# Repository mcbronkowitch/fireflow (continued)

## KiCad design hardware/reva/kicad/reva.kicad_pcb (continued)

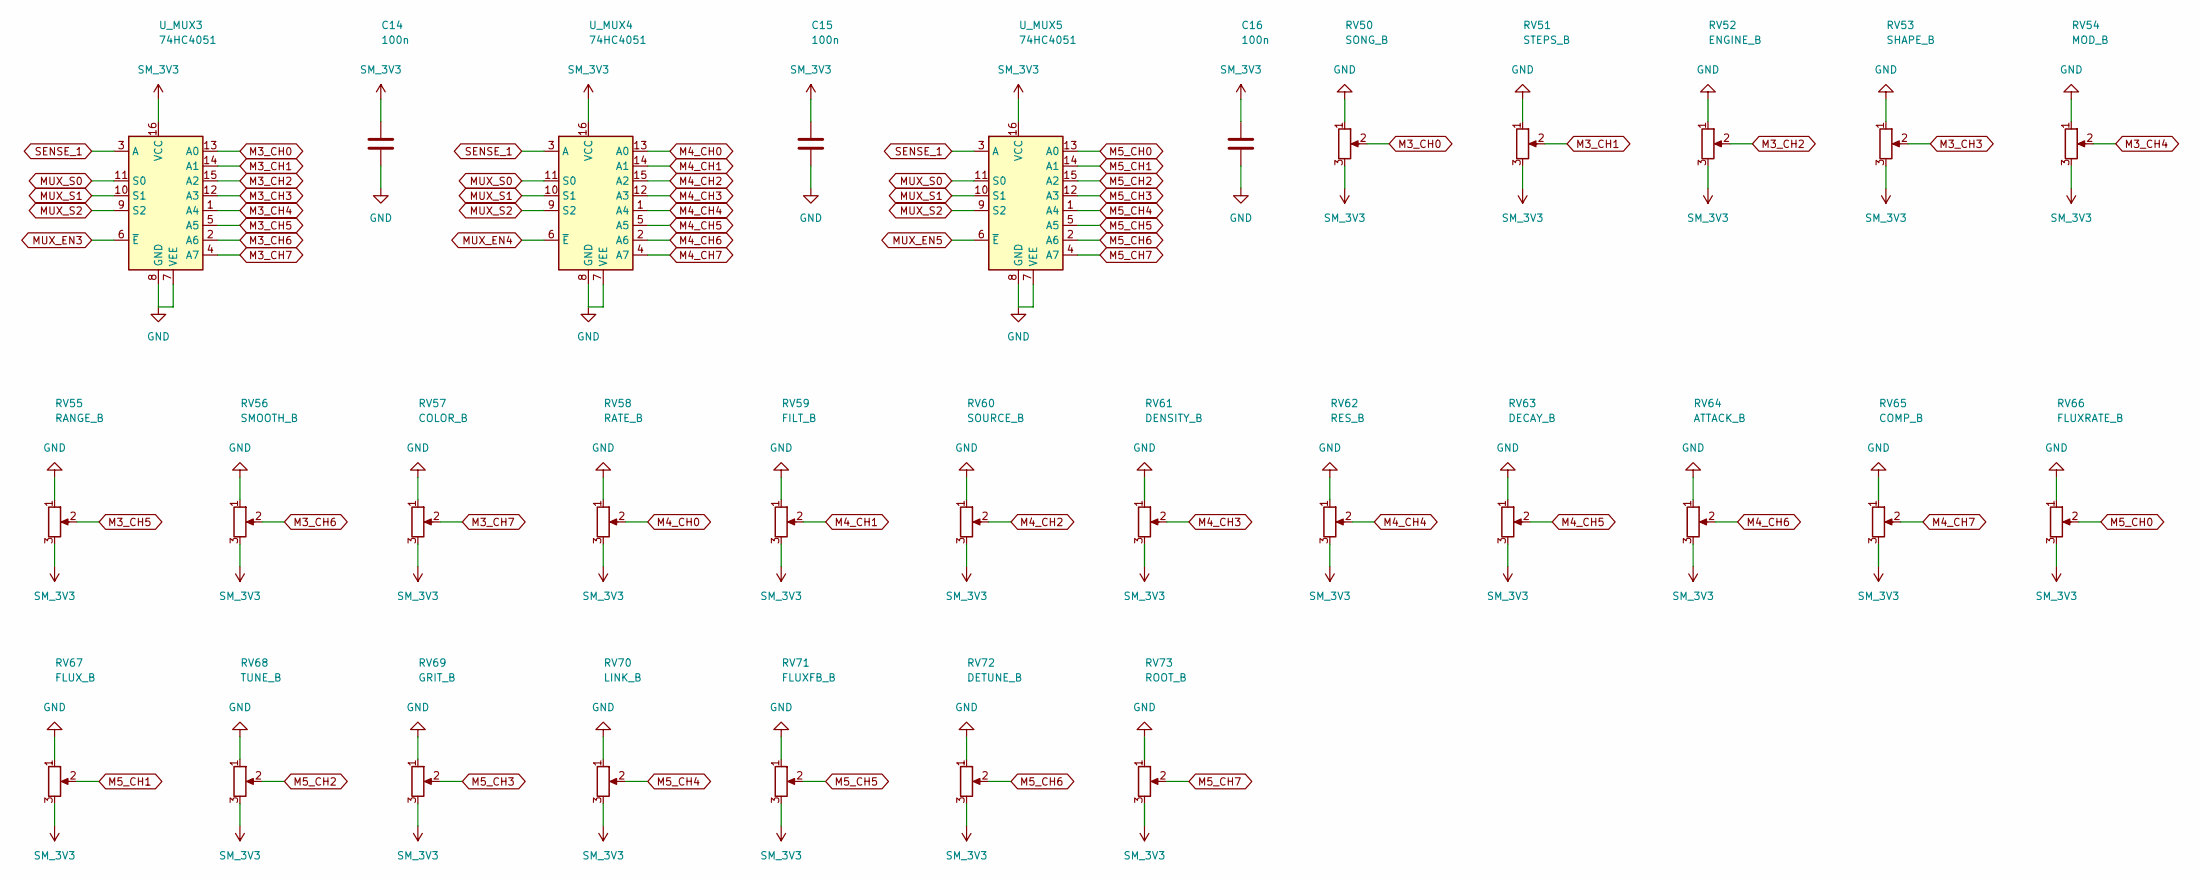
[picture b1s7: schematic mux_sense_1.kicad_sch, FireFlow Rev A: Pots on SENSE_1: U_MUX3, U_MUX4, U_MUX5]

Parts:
C14, C15, C16: 100n; C_0603_1608Metric; LCSC C14663
RV50: SONG_B; Potentiometer_Alpha_RD901F-40-00D_Single_Vertical
RV51: STEPS_B; Potentiometer_Alpha_RD901F-40-00D_Single_Vertical
RV52: ENGINE_B; Potentiometer_Alpha_RD901F-40-00D_Single_Vertical
RV53: SHAPE_B; Potentiometer_Alpha_RD901F-40-00D_Single_Vertical
RV54: MOD_B; Potentiometer_Alpha_RD901F-40-00D_Single_Vertical
RV55: RANGE_B; Potentiometer_Alpha_RD901F-40-00D_Single_Vertical
RV56: SMOOTH_B; Potentiometer_Alpha_RD901F-40-00D_Single_Vertical
RV57: COLOR_B; Potentiometer_Alpha_RD901F-40-00D_Single_Vertical
RV58: RATE_B; Potentiometer_Alpha_RD901F-40-00D_Single_Vertical
RV59: FILT_B; Potentiometer_Alpha_RD901F-40-00D_Single_Vertical
RV60: SOURCE_B; Potentiometer_Alpha_RD901F-40-00D_Single_Vertical
RV61: DENSITY_B; Potentiometer_Alpha_RD901F-40-00D_Single_Vertical
RV62: RES_B; Potentiometer_Alpha_RD901F-40-00D_Single_Vertical
RV63: DECAY_B; Potentiometer_Alpha_RD901F-40-00D_Single_Vertical
RV64: ATTACK_B; Potentiometer_Alpha_RD901F-40-00D_Single_Vertical
RV65: COMP_B; Potentiometer_Alpha_RD901F-40-00D_Single_Vertical
RV66: FLUXRATE_B; Potentiometer_Alpha_RD901F-40-00D_Single_Vertical
RV67: FLUX_B; Potentiometer_Alpha_RD901F-40-00D_Single_Vertical
RV68: TUNE_B; Potentiometer_Alpha_RD901F-40-00D_Single_Vertical
RV69: GRIT_B; Potentiometer_Alpha_RD901F-40-00D_Single_Vertical
RV70: LINK_B; Potentiometer_Alpha_RD901F-40-00D_Single_Vertical
RV71: FLUXFB_B; Potentiometer_Alpha_RD901F-40-00D_Single_Vertical
RV72: DETUNE_B; Potentiometer_Alpha_RD901F-40-00D_Single_Vertical
RV73: ROOT_B; Potentiometer_Alpha_RD901F-40-00D_Single_Vertical
U_MUX3, U_MUX4, U_MUX5: 74HC4051; SOIC-16_3.9x9.9mm_P1.27mm; LCSC C9386

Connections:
GND: C14.2, C15.2, C16.2, RV50.1, RV51.1, RV52.1, RV53.1, RV54.1, RV55.1, RV56.1, RV57.1, RV58.1, RV59.1, RV60.1, RV61.1, RV62.1, RV63.1, RV64.1, RV65.1, RV66.1, RV67.1, RV68.1, RV69.1, RV70.1, RV71.1, RV72.1, RV73.1, U_MUX3.7 (VEE), U_MUX3.8 (GND), U_MUX4.7 (VEE), U_MUX4.8 (GND), U_MUX5.7 (VEE), U_MUX5.8 (GND); also elsewhere on the board
M3_CH0: RV50.2, U_MUX3.13 (A0)
M3_CH1: RV51.2, U_MUX3.14 (A1)
M3_CH2: RV52.2, U_MUX3.15 (A2)
M3_CH3: RV53.2, U_MUX3.12 (A3)
M3_CH4: RV54.2, U_MUX3.1 (A4)
M3_CH5: RV55.2, U_MUX3.5 (A5)
M3_CH6: RV56.2, U_MUX3.2 (A6)
M3_CH7: RV57.2, U_MUX3.4 (A7)
M4_CH0: RV58.2, U_MUX4.13 (A0)
M4_CH1: RV59.2, U_MUX4.14 (A1)
M4_CH2: RV60.2, U_MUX4.15 (A2)
M4_CH3: RV61.2, U_MUX4.12 (A3)
M4_CH4: RV62.2, U_MUX4.1 (A4)
M4_CH5: RV63.2, U_MUX4.5 (A5)
M4_CH6: RV64.2, U_MUX4.2 (A6)
M4_CH7: RV65.2, U_MUX4.4 (A7)
M5_CH0: RV66.2, U_MUX5.13 (A0)
M5_CH1: RV67.2, U_MUX5.14 (A1)
M5_CH2: RV68.2, U_MUX5.15 (A2)
M5_CH3: RV69.2, U_MUX5.12 (A3)
M5_CH4: RV70.2, U_MUX5.1 (A4)
M5_CH5: RV71.2, U_MUX5.5 (A5)
M5_CH6: RV72.2, U_MUX5.2 (A6)
M5_CH7: RV73.2, U_MUX5.4 (A7)
MUX_EN3: U_MUX3.6 (~E); also elsewhere on the board
MUX_EN4: U_MUX4.6 (~E); also elsewhere on the board
MUX_EN5: U_MUX5.6 (~E); also elsewhere on the board
MUX_S0: U_MUX3.11 (S0), U_MUX4.11 (S0), U_MUX5.11 (S0); also elsewhere on the board
MUX_S1: U_MUX3.10 (S1), U_MUX4.10 (S1), U_MUX5.10 (S1); also elsewhere on the board
MUX_S2: U_MUX3.9 (S2), U_MUX4.9 (S2), U_MUX5.9 (S2); also elsewhere on the board
SENSE_1: U_MUX3.3 (A), U_MUX4.3 (A), U_MUX5.3 (A); also elsewhere on the board
SM_3V3: C14.1, C15.1, C16.1, RV50.3, RV51.3, RV52.3, RV53.3, RV54.3, RV55.3, RV56.3, RV57.3, RV58.3, RV59.3, RV60.3, RV61.3, RV62.3, RV63.3, RV64.3, RV65.3, RV66.3, RV67.3, RV68.3, RV69.3, RV70.3, RV71.3, RV72.3, RV73.3, U_MUX3.16 (VCC), U_MUX4.16 (VCC), U_MUX5.16 (VCC); also elsewhere on the board

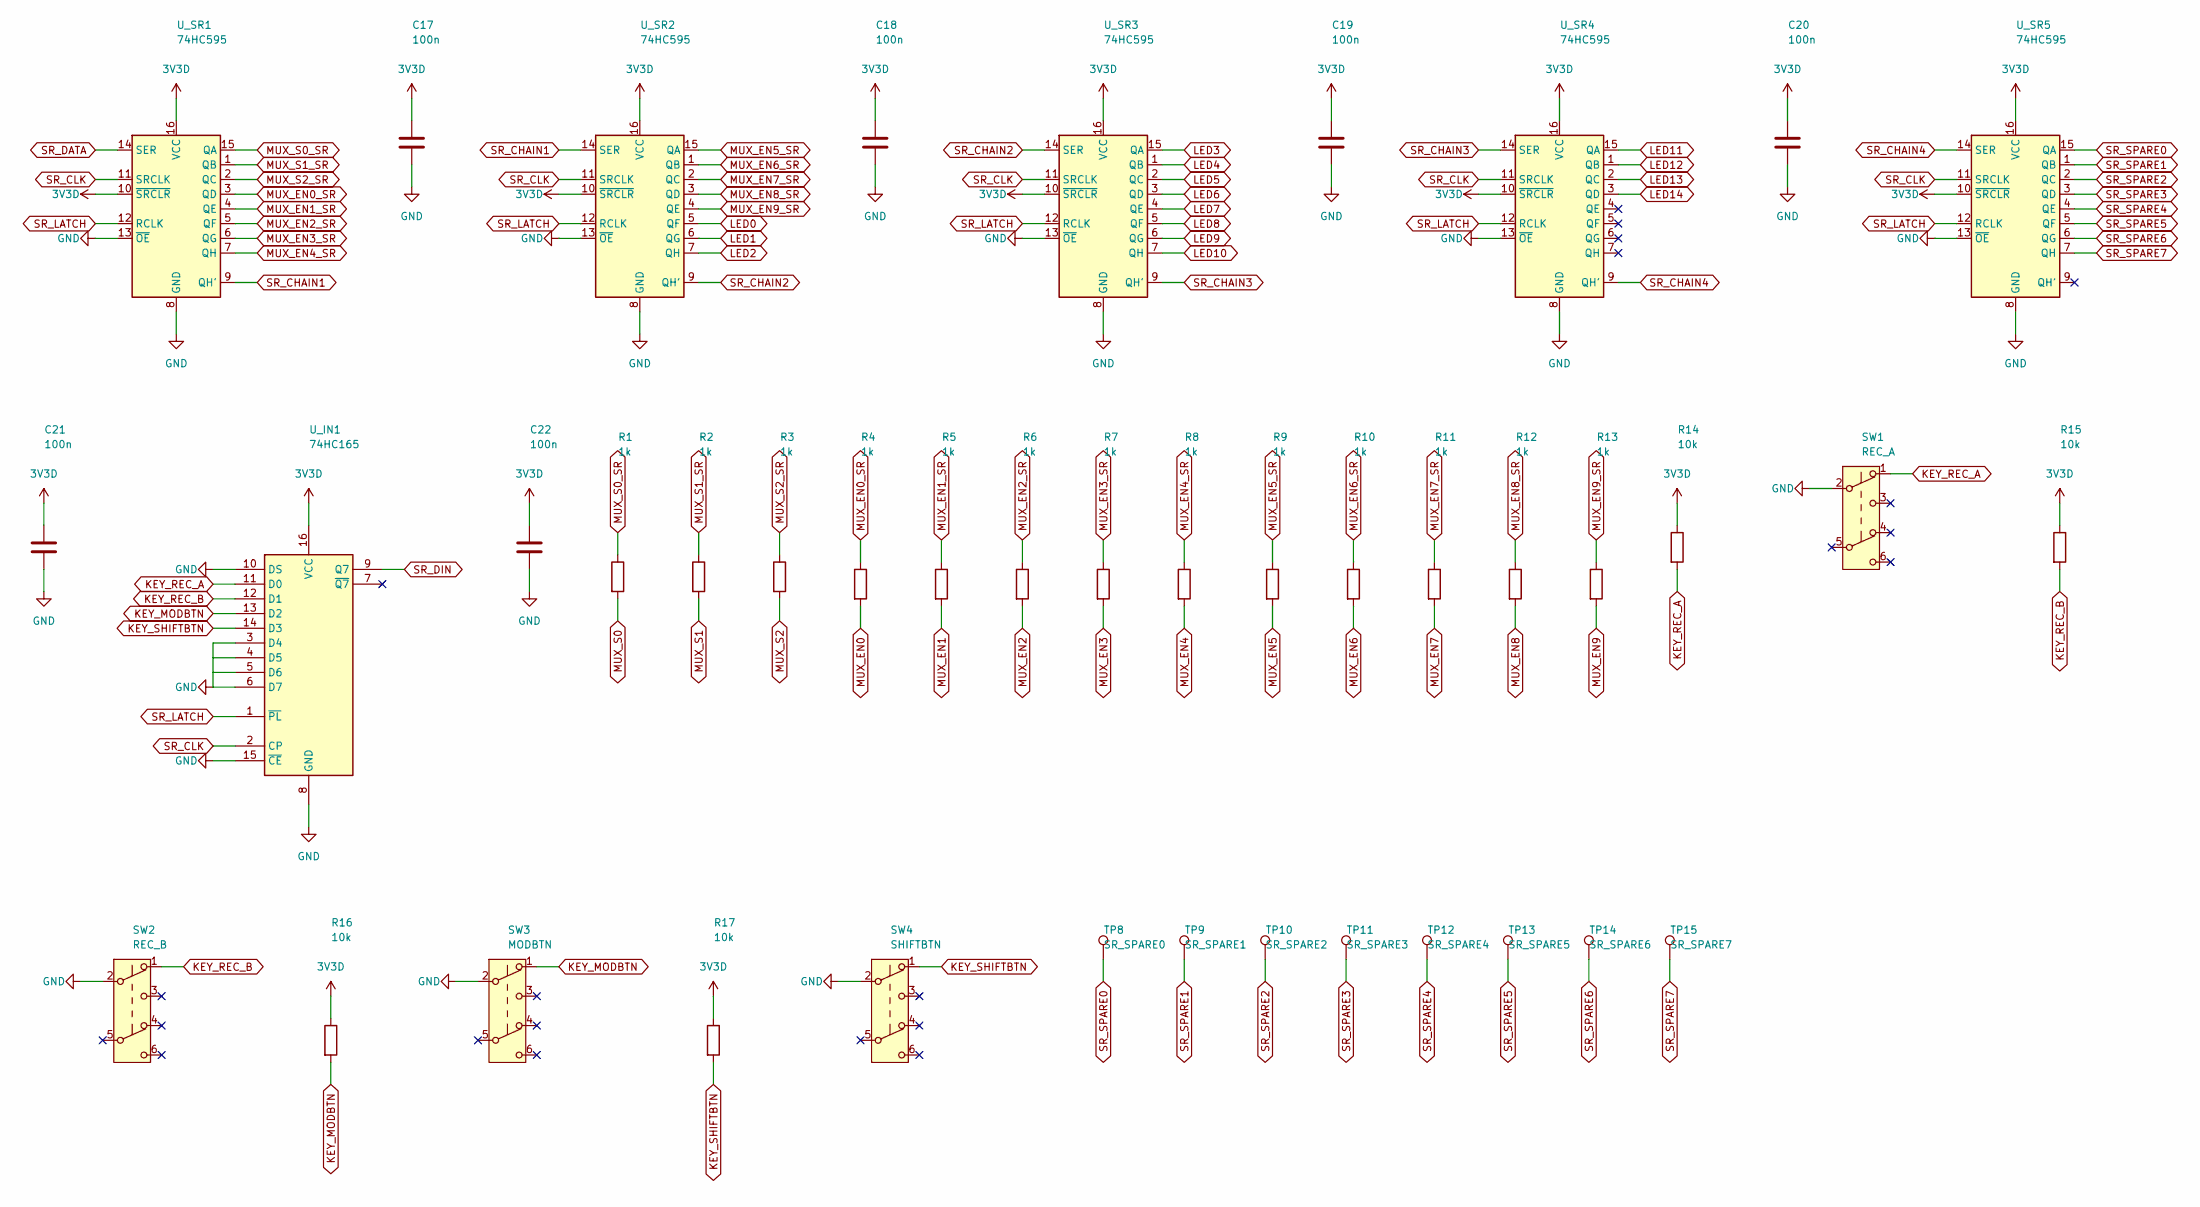
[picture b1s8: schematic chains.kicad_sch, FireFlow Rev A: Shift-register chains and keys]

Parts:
C17, C18, C19, C20, C21, C22: 100n; C_0603_1608Metric; LCSC C14663
R1, R2, R3, R4, R5, R6, R7, R8, R9, R10, R11, R12, R13: 1k; R_0603_1608Metric; LCSC C21190
R14, R15, R16, R17: 10k; R_0603_1608Metric; LCSC C25804
SW1: REC_A; SW_Push_LP_Button
SW2: REC_B; SW_Push_LP_Button
SW3: MODBTN; SW_Push_LP_Button
SW4: SHIFTBTN; SW_Push_LP_Button
TP8: SR_SPARE0; TestPoint_Pad_D1.5mm
TP9: SR_SPARE1; TestPoint_Pad_D1.5mm
TP10: SR_SPARE2; TestPoint_Pad_D1.5mm
TP11: SR_SPARE3; TestPoint_Pad_D1.5mm
TP12: SR_SPARE4; TestPoint_Pad_D1.5mm
TP13: SR_SPARE5; TestPoint_Pad_D1.5mm
TP14: SR_SPARE6; TestPoint_Pad_D1.5mm
TP15: SR_SPARE7; TestPoint_Pad_D1.5mm
U_IN1: 74HC165; SOIC-16_3.9x9.9mm_P1.27mm; LCSC C5613
U_SR1, U_SR2, U_SR3, U_SR4, U_SR5: 74HC595; SOIC-16_3.9x9.9mm_P1.27mm; LCSC C5947

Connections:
3V3D: C17.1, C18.1, C19.1, C20.1, C21.1, C22.1, R14.1, R15.1, R16.1, R17.1, U_IN1.16 (VCC), U_SR1.10 (~SRCLR), U_SR1.16 (VCC), U_SR2.10 (~SRCLR), U_SR2.16 (VCC), U_SR3.10 (~SRCLR), U_SR3.16 (VCC), U_SR4.10 (~SRCLR), U_SR4.16 (VCC), U_SR5.10 (~SRCLR), U_SR5.16 (VCC); also elsewhere on the board
GND: C17.2, C18.2, C19.2, C20.2, C21.2, C22.2, SW1.2 (B), SW2.2 (B), SW3.2 (B), SW4.2 (B), U_IN1.3 (D4), U_IN1.4 (D5), U_IN1.5 (D6), U_IN1.6 (D7), U_IN1.8 (GND), U_IN1.10 (DS), U_IN1.15 (~CE), U_SR1.8 (GND), U_SR1.13 (~OE), U_SR2.8 (GND), U_SR2.13 (~OE), U_SR3.8 (GND), U_SR3.13 (~OE), U_SR4.8 (GND), U_SR4.13 (~OE), U_SR5.8 (GND), U_SR5.13 (~OE); also elsewhere on the board
KEY_MODBTN: R16.2, SW3.1 (A), U_IN1.13 (D2)
KEY_REC_A: R14.2, SW1.1 (A), U_IN1.11 (D0)
KEY_REC_B: R15.2, SW2.1 (A), U_IN1.12 (D1)
KEY_SHIFTBTN: R17.2, SW4.1 (A), U_IN1.14 (D3)
LED0: U_SR2.5 (QF); also elsewhere on the board
LED1: U_SR2.6 (QG); also elsewhere on the board
LED2: U_SR2.7 (QH); also elsewhere on the board
LED3: U_SR3.15 (QA); also elsewhere on the board
LED4: U_SR3.1 (QB); also elsewhere on the board
LED5: U_SR3.2 (QC); also elsewhere on the board
LED6: U_SR3.3 (QD); also elsewhere on the board
LED7: U_SR3.4 (QE); also elsewhere on the board
LED8: U_SR3.5 (QF); also elsewhere on the board
LED9: U_SR3.6 (QG); also elsewhere on the board
LED10: U_SR3.7 (QH); also elsewhere on the board
LED11: U_SR4.15 (QA); also elsewhere on the board
LED12: U_SR4.1 (QB); also elsewhere on the board
LED13: U_SR4.2 (QC); also elsewhere on the board
LED14: U_SR4.3 (QD); also elsewhere on the board
MUX_EN0: R4.2; also elsewhere on the board
MUX_EN0_SR: R4.1, U_SR1.3 (QD)
MUX_EN1: R5.2; also elsewhere on the board
MUX_EN1_SR: R5.1, U_SR1.4 (QE)
MUX_EN2: R6.2; also elsewhere on the board
MUX_EN2_SR: R6.1, U_SR1.5 (QF)
MUX_EN3: R7.2; also elsewhere on the board
MUX_EN3_SR: R7.1, U_SR1.6 (QG)
MUX_EN4: R8.2; also elsewhere on the board
MUX_EN4_SR: R8.1, U_SR1.7 (QH)
MUX_EN5: R9.2; also elsewhere on the board
MUX_EN5_SR: R9.1, U_SR2.15 (QA)
MUX_EN6: R10.2; also elsewhere on the board
MUX_EN6_SR: R10.1, U_SR2.1 (QB)
MUX_EN7: R11.2; also elsewhere on the board
MUX_EN7_SR: R11.1, U_SR2.2 (QC)
MUX_EN8: R12.2; also elsewhere on the board
MUX_EN8_SR: R12.1, U_SR2.3 (QD)
MUX_EN9: R13.2; also elsewhere on the board
MUX_EN9_SR: R13.1, U_SR2.4 (QE)
MUX_S0: R1.2; also elsewhere on the board
MUX_S0_SR: R1.1, U_SR1.15 (QA)
MUX_S1: R2.2; also elsewhere on the board
MUX_S1_SR: R2.1, U_SR1.1 (QB)
MUX_S2: R3.2; also elsewhere on the board
MUX_S2_SR: R3.1, U_SR1.2 (QC)
SR_CHAIN1: U_SR1.9 (QH'), U_SR2.14 (SER)
SR_CHAIN2: U_SR2.9 (QH'), U_SR3.14 (SER)
SR_CHAIN3: U_SR3.9 (QH'), U_SR4.14 (SER)
SR_CHAIN4: U_SR4.9 (QH'), U_SR5.14 (SER)
SR_CLK: U_IN1.2 (CP), U_SR1.11 (SRCLK), U_SR2.11 (SRCLK), U_SR3.11 (SRCLK), U_SR4.11 (SRCLK), U_SR5.11 (SRCLK); also elsewhere on the board
SR_DATA: U_SR1.14 (SER); also elsewhere on the board
SR_DIN: U_IN1.9 (Q7); also elsewhere on the board
SR_LATCH: U_IN1.1 (~PL), U_SR1.12 (RCLK), U_SR2.12 (RCLK), U_SR3.12 (RCLK), U_SR4.12 (RCLK), U_SR5.12 (RCLK); also elsewhere on the board
SR_SPARE0: TP8.1, U_SR5.15 (QA)
SR_SPARE1: TP9.1, U_SR5.1 (QB)
SR_SPARE2: TP10.1, U_SR5.2 (QC)
SR_SPARE3: TP11.1, U_SR5.3 (QD)
SR_SPARE4: TP12.1, U_SR5.4 (QE)
SR_SPARE5: TP13.1, U_SR5.5 (QF)
SR_SPARE6: TP14.1, U_SR5.6 (QG)
SR_SPARE7: TP15.1, U_SR5.7 (QH)

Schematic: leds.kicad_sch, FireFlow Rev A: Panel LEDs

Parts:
D1: SHIFTBTN_L; LED_D3.0mm
D2: SONG_A_L; LED_D3.0mm
D3: GATE_A_L; LED_D3.0mm
D4: FTIME_A_L; LED_D3.0mm
D5: LVL_A_L; LED_D3.0mm
D6: REC_A_L; LED_D3.0mm
D7: CLK_L; LED_D3.0mm
D8: TEMPO_L; LED_D3.0mm
D9: RST_L; LED_D3.0mm
D10: REC_B_L; LED_D3.0mm
D11: LVL_B_L; LED_D3.0mm
D12: FTIME_B_L; LED_D3.0mm
D13: SONG_B_L; LED_D3.0mm
D14: GATE_B_L; LED_D3.0mm
D15: MODBTN_L; LED_D3.0mm
R18, R19, R20, R21, R22, R23, R24, R25, R26, R27, R28, R29, R30, R31, R32: 1k; R_0603_1608Metric; LCSC C21190

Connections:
GND: D1.1 (K), D2.1 (K), D3.1 (K), D4.1 (K), D5.1 (K), D6.1 (K), D7.1 (K), D8.1 (K), D9.1 (K), D10.1 (K), D11.1 (K), D12.1 (K), D13.1 (K), D14.1 (K), D15.1 (K); also elsewhere on the board
LED0: R18.1; also elsewhere on the board
LED0_A: D1.2 (A), R18.2
LED1: R19.1; also elsewhere on the board
LED1_A: D2.2 (A), R19.2
LED2: R20.1; also elsewhere on the board
LED2_A: D3.2 (A), R20.2
LED3: R21.1; also elsewhere on the board
LED3_A: D4.2 (A), R21.2
LED4: R22.1; also elsewhere on the board
LED4_A: D5.2 (A), R22.2
LED5: R23.1; also elsewhere on the board
LED5_A: D6.2 (A), R23.2
LED6: R24.1; also elsewhere on the board
LED6_A: D7.2 (A), R24.2
LED7: R25.1; also elsewhere on the board
LED7_A: D8.2 (A), R25.2
LED8: R26.1; also elsewhere on the board
LED8_A: D9.2 (A), R26.2
LED9: R27.1; also elsewhere on the board
LED9_A: D10.2 (A), R27.2
LED10: R28.1; also elsewhere on the board
LED10_A: D11.2 (A), R28.2
LED11: R29.1; also elsewhere on the board
LED11_A: D12.2 (A), R29.2
LED12: R30.1; also elsewhere on the board
LED12_A: D13.2 (A), R30.2
LED13: R31.1; also elsewhere on the board
LED13_A: D14.2 (A), R31.2
LED14: R32.1; also elsewhere on the board
LED14_A: D15.2 (A), R32.2

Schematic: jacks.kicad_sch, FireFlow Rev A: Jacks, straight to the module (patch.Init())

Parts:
J1: IN_L; Jack_3.5mm_QingPu_WQP-PJ398SM_Vertical_CircularHoles
J2: IN_R; Jack_3.5mm_QingPu_WQP-PJ398SM_Vertical_CircularHoles
J3: PITCH_A; Jack_3.5mm_QingPu_WQP-PJ398SM_Vertical_CircularHoles
J4: GATE_A; Jack_3.5mm_QingPu_WQP-PJ398SM_Vertical_CircularHoles
J5: MOD1_A; Jack_3.5mm_QingPu_WQP-PJ398SM_Vertical_CircularHoles
J6: MOD2_A; Jack_3.5mm_QingPu_WQP-PJ398SM_Vertical_CircularHoles
J7: MOD3_A; Jack_3.5mm_QingPu_WQP-PJ398SM_Vertical_CircularHoles
J8: MOD4_A; Jack_3.5mm_QingPu_WQP-PJ398SM_Vertical_CircularHoles
J9: CLOCK; Jack_3.5mm_QingPu_WQP-PJ398SM_Vertical_CircularHoles
J10: RESET; Jack_3.5mm_QingPu_WQP-PJ398SM_Vertical_CircularHoles
J11: MOD4_B; Jack_3.5mm_QingPu_WQP-PJ398SM_Vertical_CircularHoles
J12: MOD3_B; Jack_3.5mm_QingPu_WQP-PJ398SM_Vertical_CircularHoles
J13: MOD2_B; Jack_3.5mm_QingPu_WQP-PJ398SM_Vertical_CircularHoles
J14: MOD1_B; Jack_3.5mm_QingPu_WQP-PJ398SM_Vertical_CircularHoles
J15: GATE_B; Jack_3.5mm_QingPu_WQP-PJ398SM_Vertical_CircularHoles
J16: PITCH_B; Jack_3.5mm_QingPu_WQP-PJ398SM_Vertical_CircularHoles
J17: OUT_L; Jack_3.5mm_QingPu_WQP-PJ398SM_Vertical_CircularHoles
J18: OUT_R; Jack_3.5mm_QingPu_WQP-PJ398SM_Vertical_CircularHoles

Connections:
CLOCK: J9.T; also elsewhere on the board
GATE_A: J4.T; also elsewhere on the board
GATE_B: J15.T; also elsewhere on the board
GND: J1.S, J2.S, J3.S, J4.S, J5.S, J6.S, J7.S, J8.S, J9.S, J10.S, J11.S, J12.S, J13.S, J14.S, J15.S, J16.S, J17.S, J18.S; also elsewhere on the board
IN_L: J1.T, J2.TN; also elsewhere on the board
IN_R: J2.T; also elsewhere on the board
MOD1_A: J5.T; also elsewhere on the board
MOD1_B: J14.T; also elsewhere on the board
MOD2_A: J6.T; also elsewhere on the board
MOD2_B: J13.T; also elsewhere on the board
MOD3_A: J7.T; also elsewhere on the board
MOD3_B: J12.T; also elsewhere on the board
MOD4_A: J8.T; also elsewhere on the board
MOD4_B: J11.T; also elsewhere on the board
OUT_L: J17.T; also elsewhere on the board
OUT_R: J18.T; also elsewhere on the board
PITCH_A: J3.T; also elsewhere on the board
PITCH_B: J16.T; also elsewhere on the board
RESET: J10.T; also elsewhere on the board

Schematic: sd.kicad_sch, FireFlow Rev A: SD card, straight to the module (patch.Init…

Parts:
C_SD1: 100n; C_0603_1608Metric; LCSC C14663
C_SD2: 10u 25V; C_0805_2012Metric; LCSC C15850; not fitted
J_SD: microSD; SD_Yamaichi_PJS008U-3000-0

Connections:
GND: C_SD1.2, C_SD2.2, J_SD.6 (VSS), J_SD.SH (SHIELD); also elsewhere on the board
SD_CK: J_SD.5 (CLK); also elsewhere on the board
SD_CMD: J_SD.3 (CMD); also elsewhere on the board
SD_D0: J_SD.7 (DAT0); also elsewhere on the board
SD_D1: J_SD.8 (DAT1); also elsewhere on the board
SD_D2: J_SD.1 (DAT2); also elsewhere on the board
SD_D3: J_SD.2 (DAT3/CD); also elsewhere on the board
SM_3V3: C_SD1.1, C_SD2.1, J_SD.4 (VDD); also elsewhere on the board

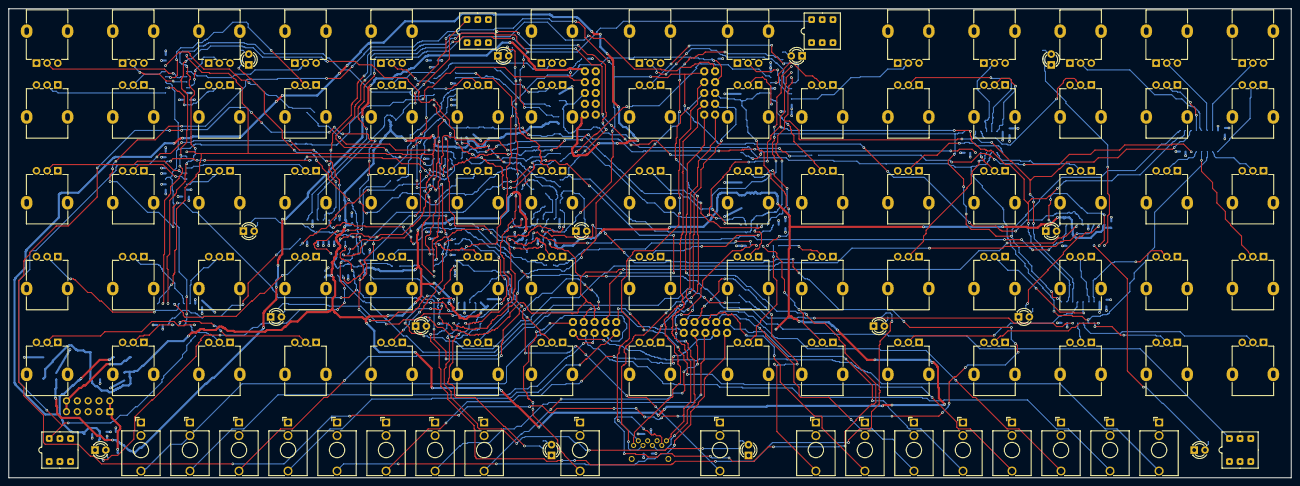
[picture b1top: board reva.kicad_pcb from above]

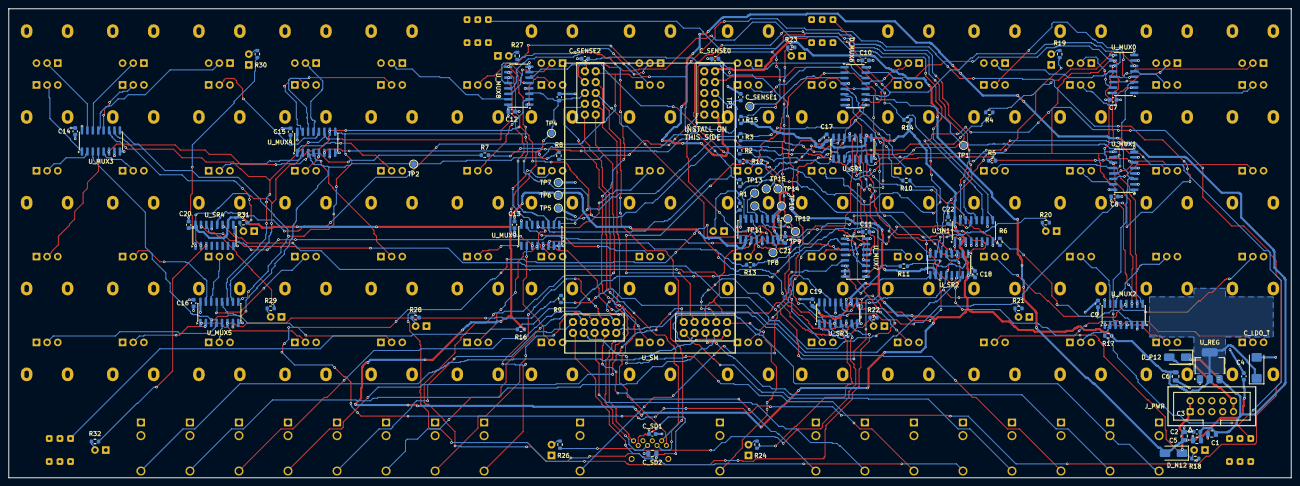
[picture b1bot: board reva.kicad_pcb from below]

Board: 4 copper layers, 300.8 x 110.0 mm, 208 parts (97 on the bottom side), 184 nets.

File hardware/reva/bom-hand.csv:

"Source","Qty","Part","Footprint","Designators"
"Electrosmith","1","Patch Submodule, socketed","DAISY_PATCH_SM","U_SM"
"Thonk","15","3 mm flat-top LED","LED_D3.0mm","D1,D2,D3,D4,D5,D6,D7,D8,D9,D10,D11,D12,D13,D14,D15"
"Thonk","73","Alpha RD901F-40 9 mm, T18 shaft, B10K","Potentiometer_Alpha_RD901F-40-00D_Single_Vertical","RV1,RV2,RV3,RV4,RV5,RV6,RV7,RV8,RV9,RV10,RV11,RV12,RV13,RV14,RV15,RV16,RV17,RV18,RV19,RV20,RV21,RV22,RV23,RV24,RV25,RV26,RV27,RV28,RV29,RV30,RV31,RV32,RV33,RV34,RV35,RV36,RV37,RV38,RV39,RV40,RV41,RV42,RV43,RV44,RV45,RV46,RV47,RV48,RV49,RV50,RV51,RV52,RV53,RV54,RV55,RV56,RV57,RV58,RV59,RV60,RV61,RV62,RV63,RV64,RV65,RV66,RV67,RV68,RV69,RV70,RV71,RV72,RV73"
"Thonk","4","Thonk low-profile button, momentary; pin 1 closes to 2","SW_Push_LP_Button","SW1,SW2,SW3,SW4"
"Thonk","18","Thonkiconn PJ398SM mono","Jack_3.5mm_QingPu_WQP-PJ398SM_Vertical_CircularHoles","J1,J2,J3,J4,J5,J6,J7,J8,J9,J10,J11,J12,J13,J14,J15,J16,J17,J18"
"hand-soldered","4","2x5 female socket for the Patch SM, cut from a 2x10 strip; its holes belong to U_SM's footprint","(no footprint)","J_SM1,J_SM2,J_SM3,J_SM4"
"hand-soldered","1","Yamaichi PJS008U-3000-0 vertical microSD, THT (P4-1 spec §4.2)","SD_Yamaichi_PJS008U-3000-0","J_SD"
"hand-soldered","1","shrouded keyed 2x5 box header; pin 1 = -12 V","IDC-Header_2x05_P2.54mm_Vertical","J_PWR"
